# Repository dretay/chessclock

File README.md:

# Trip countdown frame

A little touchscreen picture frame that counts down to your next trip: the days left on flip-clock
cards over a living picture of where you're going. The scene follows the time of day (dawn, noon,
dusk, night), with lights coming on in its windows, water rippling, smoke rising, mist in the valley,
birds and fireflies, fireworks after dark, and between them the trip's own screens: live ride wait
times, the weather there, where your ship is. It runs on a [Lichee Pi Nano](https://wiki.sipeed.com/soft/Lichee/zh/Nano-Doc-Backup/get_started/first_eye.html)
(a tiny Allwinner F1C100s board: an ARM9, 32 MB of RAM) with a 5" 800x480 touch screen.

And a **scene editor** on the Mac to make your own: drop in a photo of where you're going, and the
**Scene Builder** makes its dusk and night, finds the sky, the water and the windows, and lets you add
lights, effects and screens, watching the result live in a preview window, then install it on the
frame over USB.

## On the frame

* **The countdown:** days to go on flip-clock cards (parchment, black split-flap, wood, a departure
  board), the hours and minutes on the last day, and the trip's own greeting once you're there ("Bon
  voyage!", "Have a magical day!").
* **A living scene**, blended from day, dusk and night pictures by the real time, with effects drawn in
  C fast enough for the little ARM9: window lights that switch on and off, lights on a sphere playing
  light shows, water, foam, smoke, mist, birds, fireflies, fireworks and a nightly show.
* **Screens in turn** with the countdown: a park's live ride waits ([ThemeParks.wiki](https://themeparks.wiki)),
  a 10-day forecast with rain and snow ([Open-Meteo](https://open-meteo.com)), a map of the Disney ships
  placed by their itineraries.
* **Touch settings:** the trip's date, fireworks, which rides, display brightness by day and night,
  WiFi, and switching between trips.
* **Signed apps:** each trip is an app, signed with your key; the frame can be locked to signed apps
  (developer mode off), and can install them from your own catalog over WiFi.

The apps here: **a Disney cruise**, **Magic Kingdom**, **EPCOT**, **Universal**, **a backpacking trip**,
and **New York City**.

## On the Mac: preview and Scene Builder

```sh
tools/setup.sh                       # once: Python (uv), the fonts; --ai for "find automatically"
tools/preview/preview.py castle      # the app running in a window, the mouse as the touchscreen
```

The preview runs the real app with the device's own drawing code. Its **Controls** set the time of
day, fire the fireworks, birds or fireflies, and (**Remote**) do the same on the frame over USB. Its
**Scene Builder** panel, docked beside it:

* **New…** a trip (a name, a park's ride waits, a place's weather), or pick an existing one;
* **Photos:** drop a photo to try it as the scene (each a trial, kept in the app when you like it);
  zoomed in, you paint on the original photo at full resolution;
* **Layout:** where the countdown sits, its size, the card style, the horizon;
* **Effects:** lights on a sphere and their shows; window lights (painted, boxed, found, with frames
  kept dark in front and windows grouped to switch together); water and foam; smoke, mist and birds;
  fireworks and fireflies;
* **Screens:** ride waits, weather (place checked), the ship map, and for how long each shows;
* **On the device:** install it on the frame, signed or not.

Every change is saved as you go. More in [the tools](docs/tools.md).

## Hardware

| Part | Notes |
|---|---|
| [Lichee Pi Nano](https://wiki.sipeed.com/soft/Lichee/zh/Nano-Doc-Backup/get_started/first_eye.html) | Allwinner F1C100s, 32 MB RAM, boots from microSD; run at 600 MHz (its own 408: `CPU_MHZ` in the device's settings) |
| 5" 800x480 40-pin RGB TFT with 4-wire resistive touch | e.g. the F50GLQ24E22: its ribbon plugs straight into the Nano, the touch film's tail to the ribbon's last four pins |
| microSD card | any size; the image is about 200 MB |
| 5 V USB power and a micro-USB cable | the micro-USB port is also the tools' fast serial line to the Mac |
| *Optional:* an ESP32 | WiFi, on the SPI bus ([wifi](docs/wifi.md)), for live waits, weather, ship positions, the catalog and the clock |
| *Optional:* a PAM8403 amplifier and a speaker | sound, from the chip's own audio codec ([system](docs/system.md)) |
| *Optional:* the [3D-printed enclosure](hardware/enclosure) | picture frame, back cover and desk cradle |
| *Optional:* a 3.3 V USB-serial adapter | the console on UART0, 115200 baud |

A custom board with the 64 MB F1C200s, the ESP32, the amplifier and room to tinker is designed in
[hardware/protoboard](hardware/protoboard). The board has no battery-backed clock: the frame keeps the
time on the SD card across power cuts, and sets it from the network with WiFi.

## Building and flashing

```sh
tools/build/build.sh --wifi                      # the base system (the first time: 1-2 hours)
tools/board/flash_sd.sh --all build/images-wifi  # the SD card (macOS; asks first)
tools/board/deploy.py --signed system countdown castle   # then apps go over USB: no reflashing
```

The SD card holds a read-only base system and, on a partition of their own, the apps and their
settings: changing an app never means rebuilding the image, and reflashing the base keeps the apps.
[Building and flashing](docs/building.md) has the details. `tools/test/check.py` checks everything,
rendering every scene and comparing it pixel for pixel with the last time.

## Documentation

| | |
|---|---|
| [docs/countdown.md](docs/countdown.md) | the countdown apps: their scenes, effects, screens and settings |
| [docs/tools.md](docs/tools.md) | the Mac tools: setup, the preview and Scene Builder, deploying, checking |
| [docs/apps.md](docs/apps.md) | what an app is: laid out, started, switched, signed, installed, the catalog, developer mode |
| [docs/system.md](docs/system.md) | how the system works: kernel, device tree, boot, memory, sound, security |
| [docs/wifi.md](docs/wifi.md) | WiFi through an ESP32: wiring, firmware, the wiring check and wiring test |
| [docs/building.md](docs/building.md) | building the base system and flashing the card |
| [apps/countdown/README.md](apps/countdown/README.md) | the countdown runtime |
| [tools/themegen/README.md](tools/themegen/README.md) | how scenes are made and packed |
| [hardware/](hardware) | the enclosure, and the protoboard (KiCad) |

## Repository layout

| Path | |
|---|---|
| `apps/` | one folder per app (`app.json`, `run`, its scene): `cruise`, `castle`, `epcot`, `universal`, `backpacking`, `new-york-city`; `countdown` (the runtime the trips share: the countdown, its screens and their fetchers) and `system` (what every app shares: the C drawing library, Settings, Device settings, WiFi, the picker) |
| `tools/preview/` | the preview window (Swift), the Scene Builder (a web page in it), and the server between them |
| `tools/themegen/` | making scenes from photos (`photo_scene.py`), packing them (`scene_pack.py`), icons, splashes, the ship map |
| `tools/apps/` | new apps, packing and signing them, publishing the catalog |
| `tools/board/` | talking to the board over USB: deploy, run, flash the card |
| `tools/build/` | incremental base-system builds in a container |
| `tools/wifi/` | the ESP32's WiFi firmware, and its wiring-test firmware |
| `tools/test/` | the checks |
| `board/licheepi_nano/`, `configs/`, `package/` | the Buildroot `BR2_EXTERNAL` tree: kernel config, patches and device tree, U-Boot, the SD card layout, the boot scripts (Buildroot itself is unmodified) |
| `hardware/` | the enclosure and the protoboard |
| `docs/` | the documentation above |
| `pyproject.toml`, `uv.lock`, `.python-version` | the Mac tools' Python (`tools/setup.sh`) |
| `Dockerfile.base` | the base image: the cross-compiler and a first build (then `tools/build/build.sh`) |
| `assets/` | (not in the repository) source photos and fonts |

## Credits

The Buildroot setup started from [unframework/licheepi-nano-buildroot](https://github.com/unframework/licheepi-nano-buildroot), which in turn adapted the FunKey Zero project's [buildroot-licheepi-zero](https://github.com/Squonk42/buildroot-licheepi-zero/). The F1C100s kernel and U-Boot work comes from @Icenowy, @Lichee-Pi and @unframework. Ride waits from [ThemeParks.wiki](https://themeparks.wiki), weather from [Open-Meteo](https://open-meteo.com), ship schedules from [CruiseMapper](https://www.cruisemapper.com). The scenes made from photos of Disney and Universal parks and ships are for personal use; Disney and Universal names and places are their owners' trademarks.

Licensed under the GPL-3.0 (see [LICENSE](LICENSE)).

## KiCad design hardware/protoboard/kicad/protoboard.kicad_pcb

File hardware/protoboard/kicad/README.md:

# F1C200s protoboard - KiCad project

KiCad 10 project for the board specified in [`../DESIGN.md`](../DESIGN.md):
118 x 72.5 mm, 4 layers: F.Cu signals + GND pour / In1 solid GND (no tracks) /
In2 signals + +3V3 pour / B.Cu signals + GND pour.

| File | |
|---|---|
| `protoboard.kicad_pro` | project, design rules (0.127 mm clearance, 0.1 mm min track for the router's neck-downs at the QFN, 0.2 mm drill) and netclasses (Default, Power, HighCurrent, USB) |
| `protoboard.kicad_sch` | root sheet, with sub-sheets `power`, `soc`, `display`, `storage`, `wifi`, `audio`, `io` |
| `protoboard.kicad_pcb` | placed for the desk stand (LCD connector front-right, USB-C/microSD/5V IN on the back edge) and autorouted, 5 connections left by hand (see below), pours filled, ESP antenna keep-out |
| `lib/` | custom symbols (F1C200s, SY8089, PT4103, NS2009, ESP32-C3 SuperMini) and footprints (SuperMini for headers or flat soldering, F1C QFN-88 with 0.22 mm pads, prototyping grid, rail strips) |
| `gen/` | the generator |

## Generated, not hand-drawn

`gen/design.py` holds the whole netlist: every part, value, footprint and
pin-to-net assignment, block by block following DESIGN.md. The rest is
derived from it:

```sh
./gen/build.sh            # libs -> schematic -> netlist -> PCB, then ERC + DRC (reports in gen/.cache/)
./gen/build.sh --sch-only # stop after the schematic
```

* `gen_sch.py` places the symbols on each sheet and connects every pin with a
  power symbol, a label or a no-connect flag. Nothing is wired, so
  connectivity comes only from net names.
* `gen_pcb.py` (run with KiCad's own Python) reads the netlist KiCad exports
  from the schematic, so the board stays in parity with it. It fixes the parts
  whose position the spec decides (FPC, USB-C, microSD, ESP, buttons,
  breakouts, rails, holes) and packs the rest as close as possible to the pads
  they connect to.

**Rerunning `build.sh` overwrites the .kicad_sch and .kicad_pcb files.** Once
you start routing or moving parts by hand, stop regenerating the PCB: make
schematic changes in KiCad and use *Update PCB from Schematic*. Or keep
editing `design.py`, but only with `--sch-only`.

## Routing

The board was autorouted with [Freerouting](https://github.com/freerouting/freerouting)
2.5 (needs Java 25+):

```sh
FREEROUTING_JAR=/path/to/freerouting.jar JAVA=/path/to/java ./gen/route.sh 40        # fresh route
FREEROUTING_JAR=... KEEP_TRACKS=1 ./gen/route.sh 40                                   # continue from the current tracks
WORK=gen/.cache/try1 ./gen/route.sh                                                   # route a copy instead
```

`route.sh` exports a Specctra DSN (`route.py export`, with pours and
stitching vias stripped), runs Freerouting with `gen/freerouting.rules`
(In1 inactive, so the GND plane gets vias but no tracks), imports the session,
then in a fresh process (`route.py post`) fixes undersized via rings, pours
+3V3 on In2 and GND on F.Cu/B.Cu, adds GND stitching vias wherever one fits
inside an outer pour, refills, and finally removes any via DRC flags as
dangling or (for GND vias) too close to something (two rounds: removing a
via can leave a neighbour dangling).

`build.sh` refuses to regenerate a routed board (`FORCE=1` overrides, which
throws the routing away). `gen_pcb.py` reproduces the routed board's
placement exactly, so a reroute is `FORCE=1 ./gen/build.sh` then
`./gen/route.sh 30`.

### What made it routable

Freerouting gets almost all of its result in the first run: continuation
passes (`KEEP_TRACKS=1`) never improved a board, and two runs of the same
placement differed by 22 vs 56 unconnected, so it pays to try several
placements in parallel (one core each) rather than run one longer. Fixes:

* **Board 118 x 72.5 mm and 0.25 mm extra spacing around every part**
  (`BOARD_W`, `BOARD_H`, `PLACE_GAP` in `gen_pcb.py`). On the stand layout
  0.25 gave 5 unconnected where 0.15/0.2 gave 14-57.
* **SoC rotated 180 degrees** (`SOC_ROT`): the LCD connector is right of the
  chip, and 180 lets the power pins escape far better than 90 (13 vs 28+).
* **Buck order** (`BUCK_X`): the three SY8089 bucks along the front edge.
* **microSD on the back edge.** `SD_SIDE=1` puts it on the right edge instead
  (and gives the protogrid back its full 38 columns, rails 32 holes), but the
  best of six routes was 19 unconnected against 5, so it isn't the default.
* **+1V1 area on In2** (added by `route.py post`, priority over the +3V3
  pour) from the core buck to under the SoC, plus `gen/viafix.py`, which
  drops a via into it from any +1V1 pad or track end the router left.
* **0.5 mm no-track strip** along the board edges (the router hugged them).
* **Ribbon keep-out:** connectors, switches and through-hole parts stay out
  of the area the LCD ribbon lies over between the front edge and the FPC.
* **QFN fan-out area:** the strip between the SoC and the FPC is kept free
  of parts for the LCD lines and their vias.
* **Placement order:** crystal and its caps first, then the SoC decoupling
  caps, each one next to a power pin of its own chip.
* **In1 stays a solid plane.** Letting the router use In1 (`gen/freerouting_in1.rules`)
  got to 7 unconnected on its own but broke the GND plane into 44 islands,
  so it isn't used.

### Finishing by hand

* **+2V5, SoC pin 36:** a 0.8 mm gap to its own track end; the straight line
  passes +1V1 pin 35, so come in from outside the pin row.
* **RESET (2):** SoC pin 70 to its pull-up R16, and R16 to the RESET button's
  track on B.Cu (stub at x 47.5, y 31).
* **GND (2):** two pour islands; KiCad's ratsnest shows them - a via each.
* 199 `track_width` are the router's 0.112 mm neck-downs into the QFN pads
  (allowed by the 0.1 mm board minimum, flagged against the netclass width).
* Silkscreen overlaps.

## State

* ERC: 0 violations. DRC: 0 clearance, short or courtyard errors, schematic
  parity clean; 5 unconnected, listed above.
* Test points are on the bottom side.
* R/C/L designators are on F.Fab (the assembly drawing). The board is too
  dense for them on silk.
* Open items are listed at the end of DESIGN.md.

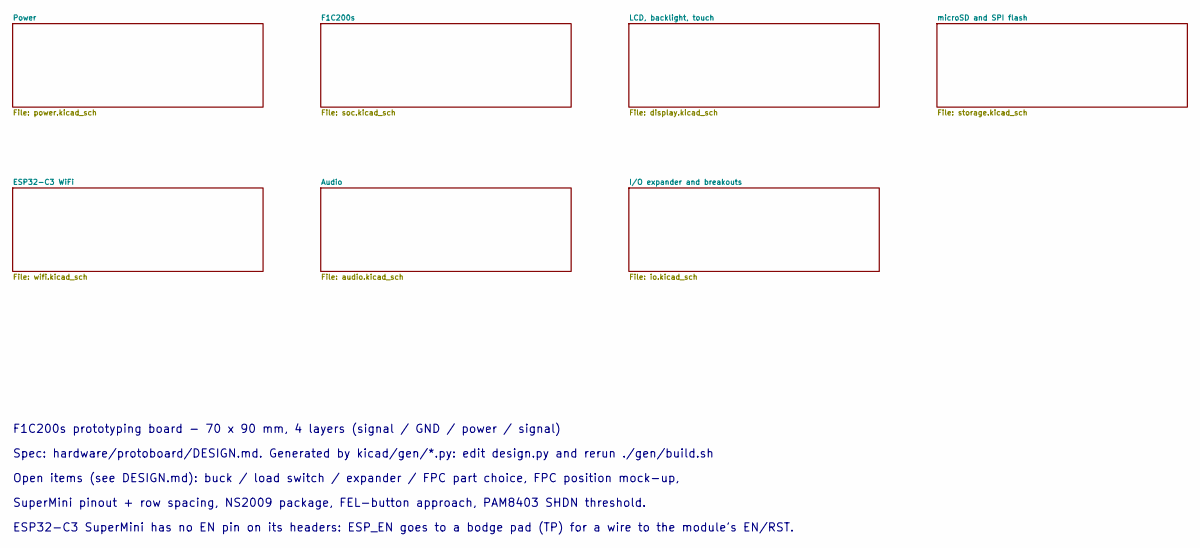
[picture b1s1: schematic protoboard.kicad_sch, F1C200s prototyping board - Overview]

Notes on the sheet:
F1C200s prototyping board - 70 x 90 mm, 4 layers (signal / GND / power / signal)
Spec: hardware/protoboard/DESIGN.md. Generated by kicad/gen/*.py: edit design.py and rerun ./gen/build.sh
Open items (see DESIGN.md): buck / load switch / expander / FPC part choice, FPC position mock-up,
SuperMini pinout + row spacing, NS2009 package, FEL-button approach, PAM8403 SHDN threshold.
ESP32-C3 SuperMini has no EN pin on its headers: ESP_EN goes to a bodge pad (TP) for a wire to the module's EN/RST.

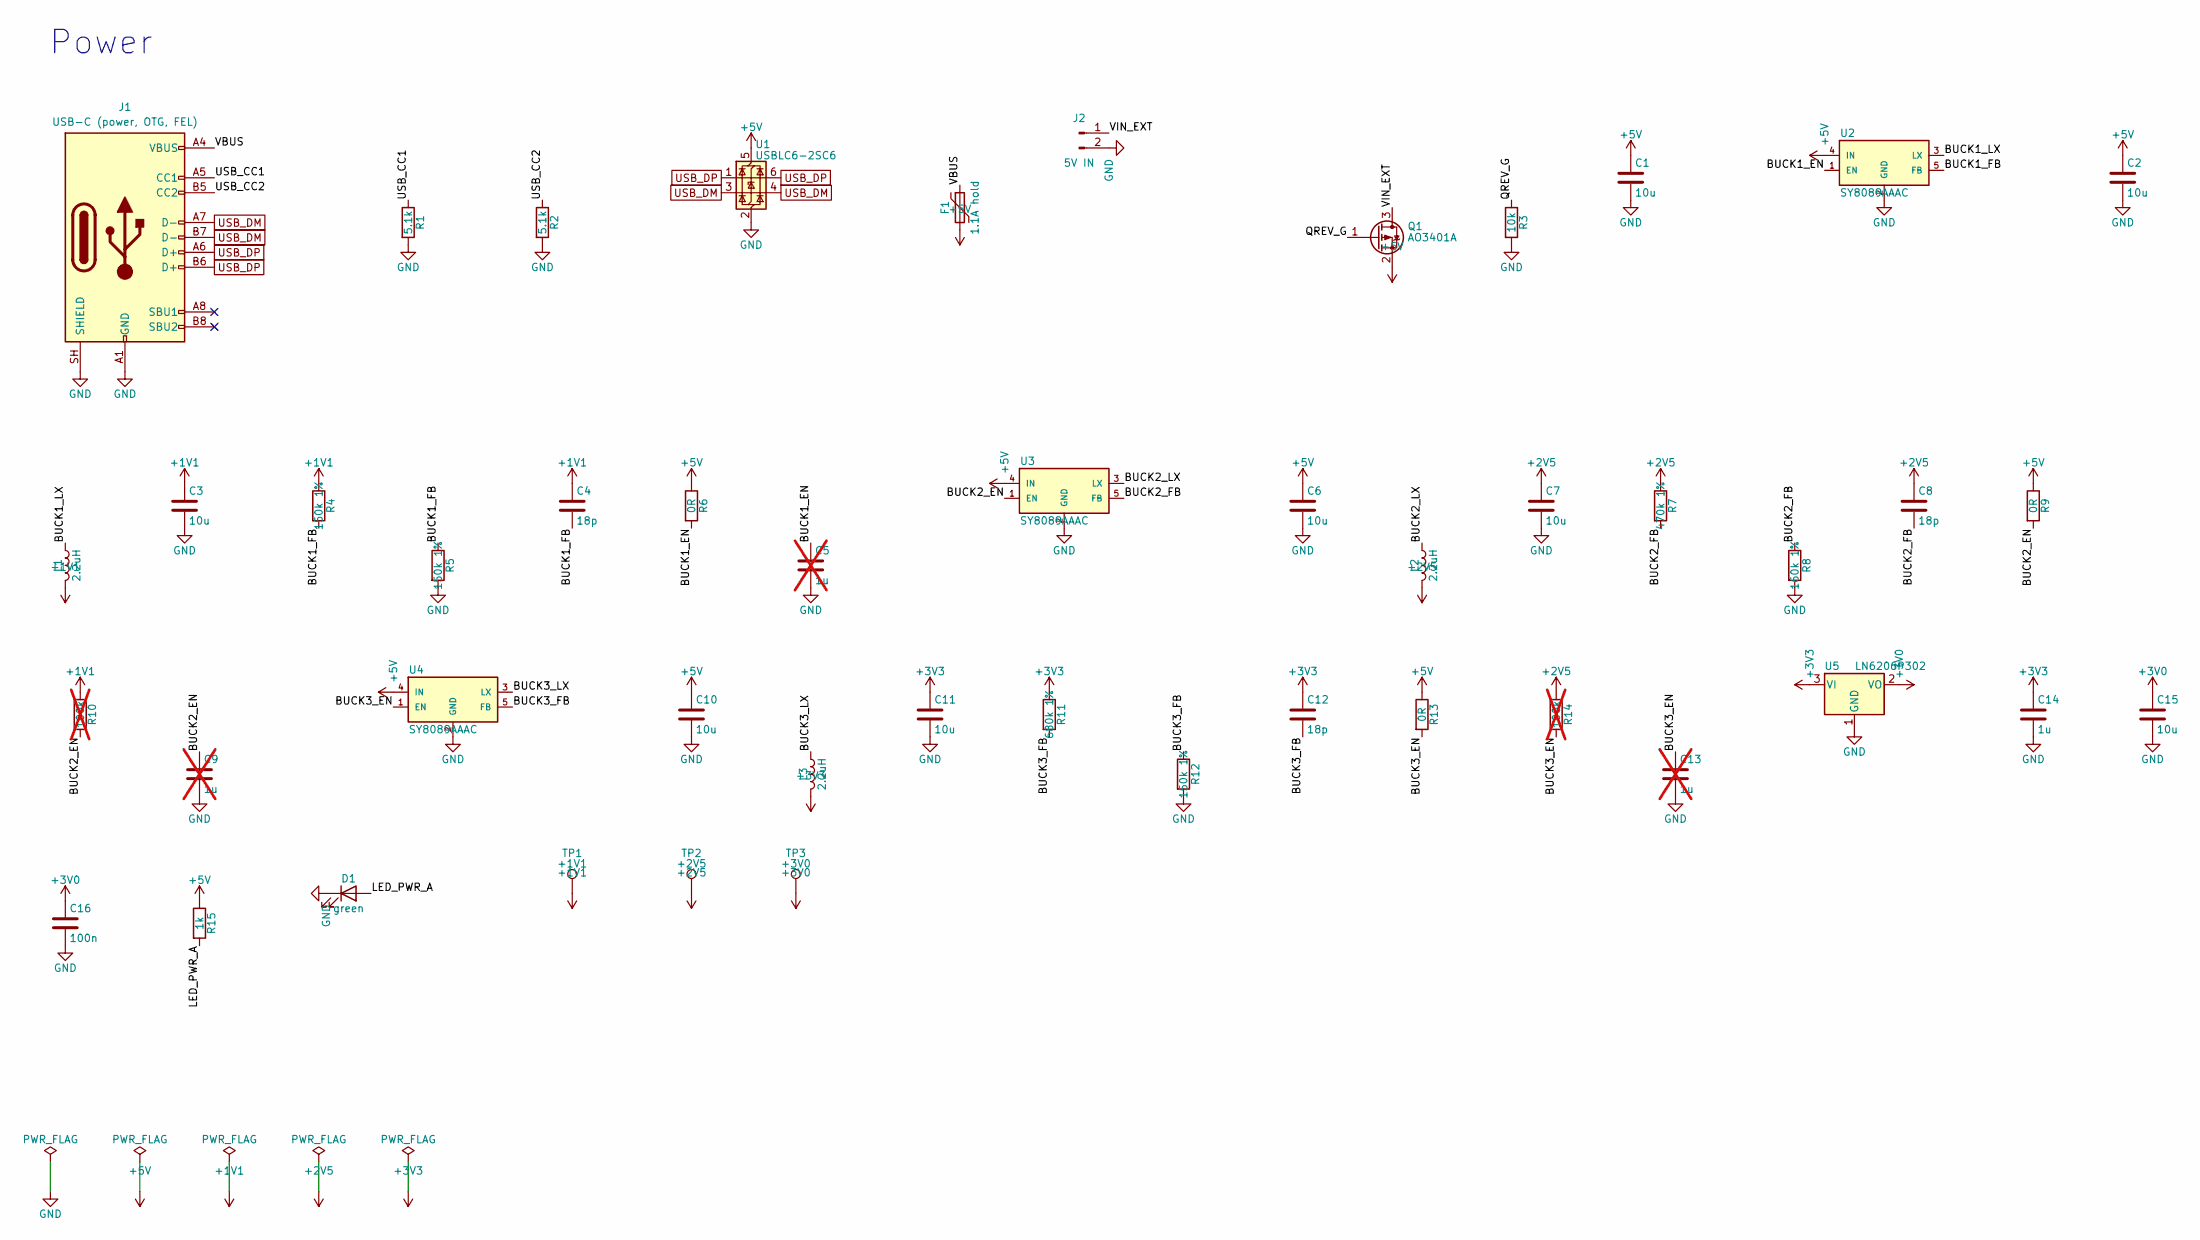
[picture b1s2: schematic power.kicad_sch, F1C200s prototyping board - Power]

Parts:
C1, C2, C3, C6, C7, C10, C11: 10u; C_1206_3216Metric_Pad1.33x1.80mm_HandSolder
C4, C8, C12: 18p; C_0805_2012Metric_Pad1.18x1.45mm_HandSolder
C5, C9, C13: 1u; C_0805_2012Metric_Pad1.18x1.45mm_HandSolder; not fitted
C14: 1u; C_0805_2012Metric_Pad1.18x1.45mm_HandSolder
C15: 10u; C_0805_2012Metric_Pad1.18x1.45mm_HandSolder
C16: 100n; C_0805_2012Metric_Pad1.18x1.45mm_HandSolder
D1: green; LED_0805_2012Metric_Pad1.15x1.40mm_HandSolder
F1: 1.1A hold; Fuse_1206_3216Metric_Pad1.42x1.75mm_HandSolder
J1: USB-C (power, OTG, FEL); USB_C_Receptacle_HRO_TYPE-C-31-M-12
J2: 5V IN; TerminalBlock_Phoenix_PT-1,5-2-3.5-H_1x02_P3.50mm_Horizontal
L1, L2, L3: 2.2uH; L_Bourns-SRN4018
Q1: AO3401A; SOT-23
R1, R2: 5.1k; R_0805_2012Metric_Pad1.20x1.40mm_HandSolder
R3: 10k; R_0805_2012Metric_Pad1.20x1.40mm_HandSolder
R4, R5, R12: 150k 1%; R_0805_2012Metric_Pad1.20x1.40mm_HandSolder
R6, R9, R13: 0R; R_0805_2012Metric_Pad1.20x1.40mm_HandSolder
R7: 470k 1%; R_0805_2012Metric_Pad1.20x1.40mm_HandSolder
R8: 160k 1%; R_0805_2012Metric_Pad1.20x1.40mm_HandSolder
R10, R14: 100k; R_0805_2012Metric_Pad1.20x1.40mm_HandSolder; not fitted
R11: 680k 1%; R_0805_2012Metric_Pad1.20x1.40mm_HandSolder
R15: 1k; R_0805_2012Metric_Pad1.20x1.40mm_HandSolder
TP1: +1V1; TestPoint_Pad_D1.5mm
TP2: +2V5; TestPoint_Pad_D1.5mm
TP3: +3V0; TestPoint_Pad_D1.5mm
U1: USBLC6-2SC6; SOT-23-6
U2, U3, U4: SY8089AAAC; SOT-23-5
U5: LN6206P302; SOT-23-3

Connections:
+1V1: C3.1, C4.1, L1.2, R4.1, R10.1, TP1.1; also elsewhere on the board
+2V5: C7.1, C8.1, L2.2, R7.1, R14.1, TP2.1; also elsewhere on the board
+3V0: C15.1, C16.1, TP3.1, U5.2 (VO); also elsewhere on the board
+3V3: C11.1, C12.1, C14.1, L3.2, R11.1, U5.3 (VI); also elsewhere on the board
+5V: C1.1, C2.1, C6.1, C10.1, F1.2, Q1.2 (S), R6.1, R9.1, R13.1, R15.1, U1.5 (VBUS), U2.4 (IN), U3.4 (IN), U4.4 (IN); also elsewhere on the board
/Power/BUCK1_EN: C5.1, R6.2, U2.1 (EN)
/Power/BUCK1_FB: C4.2, R4.2, R5.1, U2.5 (FB)
/Power/BUCK1_LX: L1.1, U2.3 (LX)
/Power/BUCK2_EN: C9.1, R9.2, R10.2, U3.1 (EN)
/Power/BUCK2_FB: C8.2, R7.2, R8.1, U3.5 (FB)
/Power/BUCK2_LX: L2.1, U3.3 (LX)
/Power/BUCK3_EN: C13.1, R13.2, R14.2, U4.1 (EN)
/Power/BUCK3_FB: C12.2, R11.2, R12.1, U4.5 (FB)
/Power/BUCK3_LX: L3.1, U4.3 (LX)
/Power/LED_PWR_A: D1.2 (A), R15.2
/Power/QREV_G: Q1.1 (G), R3.1
/Power/USB_CC1: J1.A5 (CC1), R1.1
/Power/USB_CC2: J1.B5 (CC2), R2.1
/Power/VBUS: F1.1, J1.A4 (VBUS), J1.A9 (VBUS), J1.B4 (VBUS), J1.B9 (VBUS)
/Power/VIN_EXT: J2.1, Q1.3 (D)
GND: C1.2, C2.2, C3.2, C5.2, C6.2, C7.2, C9.2, C10.2, C11.2, C13.2, C14.2, C15.2, C16.2, D1.1 (K), J1.A1 (GND), J1.A12 (GND), J1.B1 (GND), J1.B12 (GND), J1.SH (SHIELD), J2.2, R1.2, R2.2, R3.2, R5.2, R8.2, R12.2, U1.2 (GND), U2.2 (GND), U3.2 (GND), U4.2 (GND), U5.1 (GND); also elsewhere on the board
USB_DM: J1.A7 (D-), J1.B7 (D-), U1.3 (I/O2), U1.4 (I/O2); also elsewhere on the board
USB_DP: J1.A6 (D+), J1.B6 (D+), U1.1 (I/O1), U1.6 (I/O1); also elsewhere on the board

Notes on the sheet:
Power

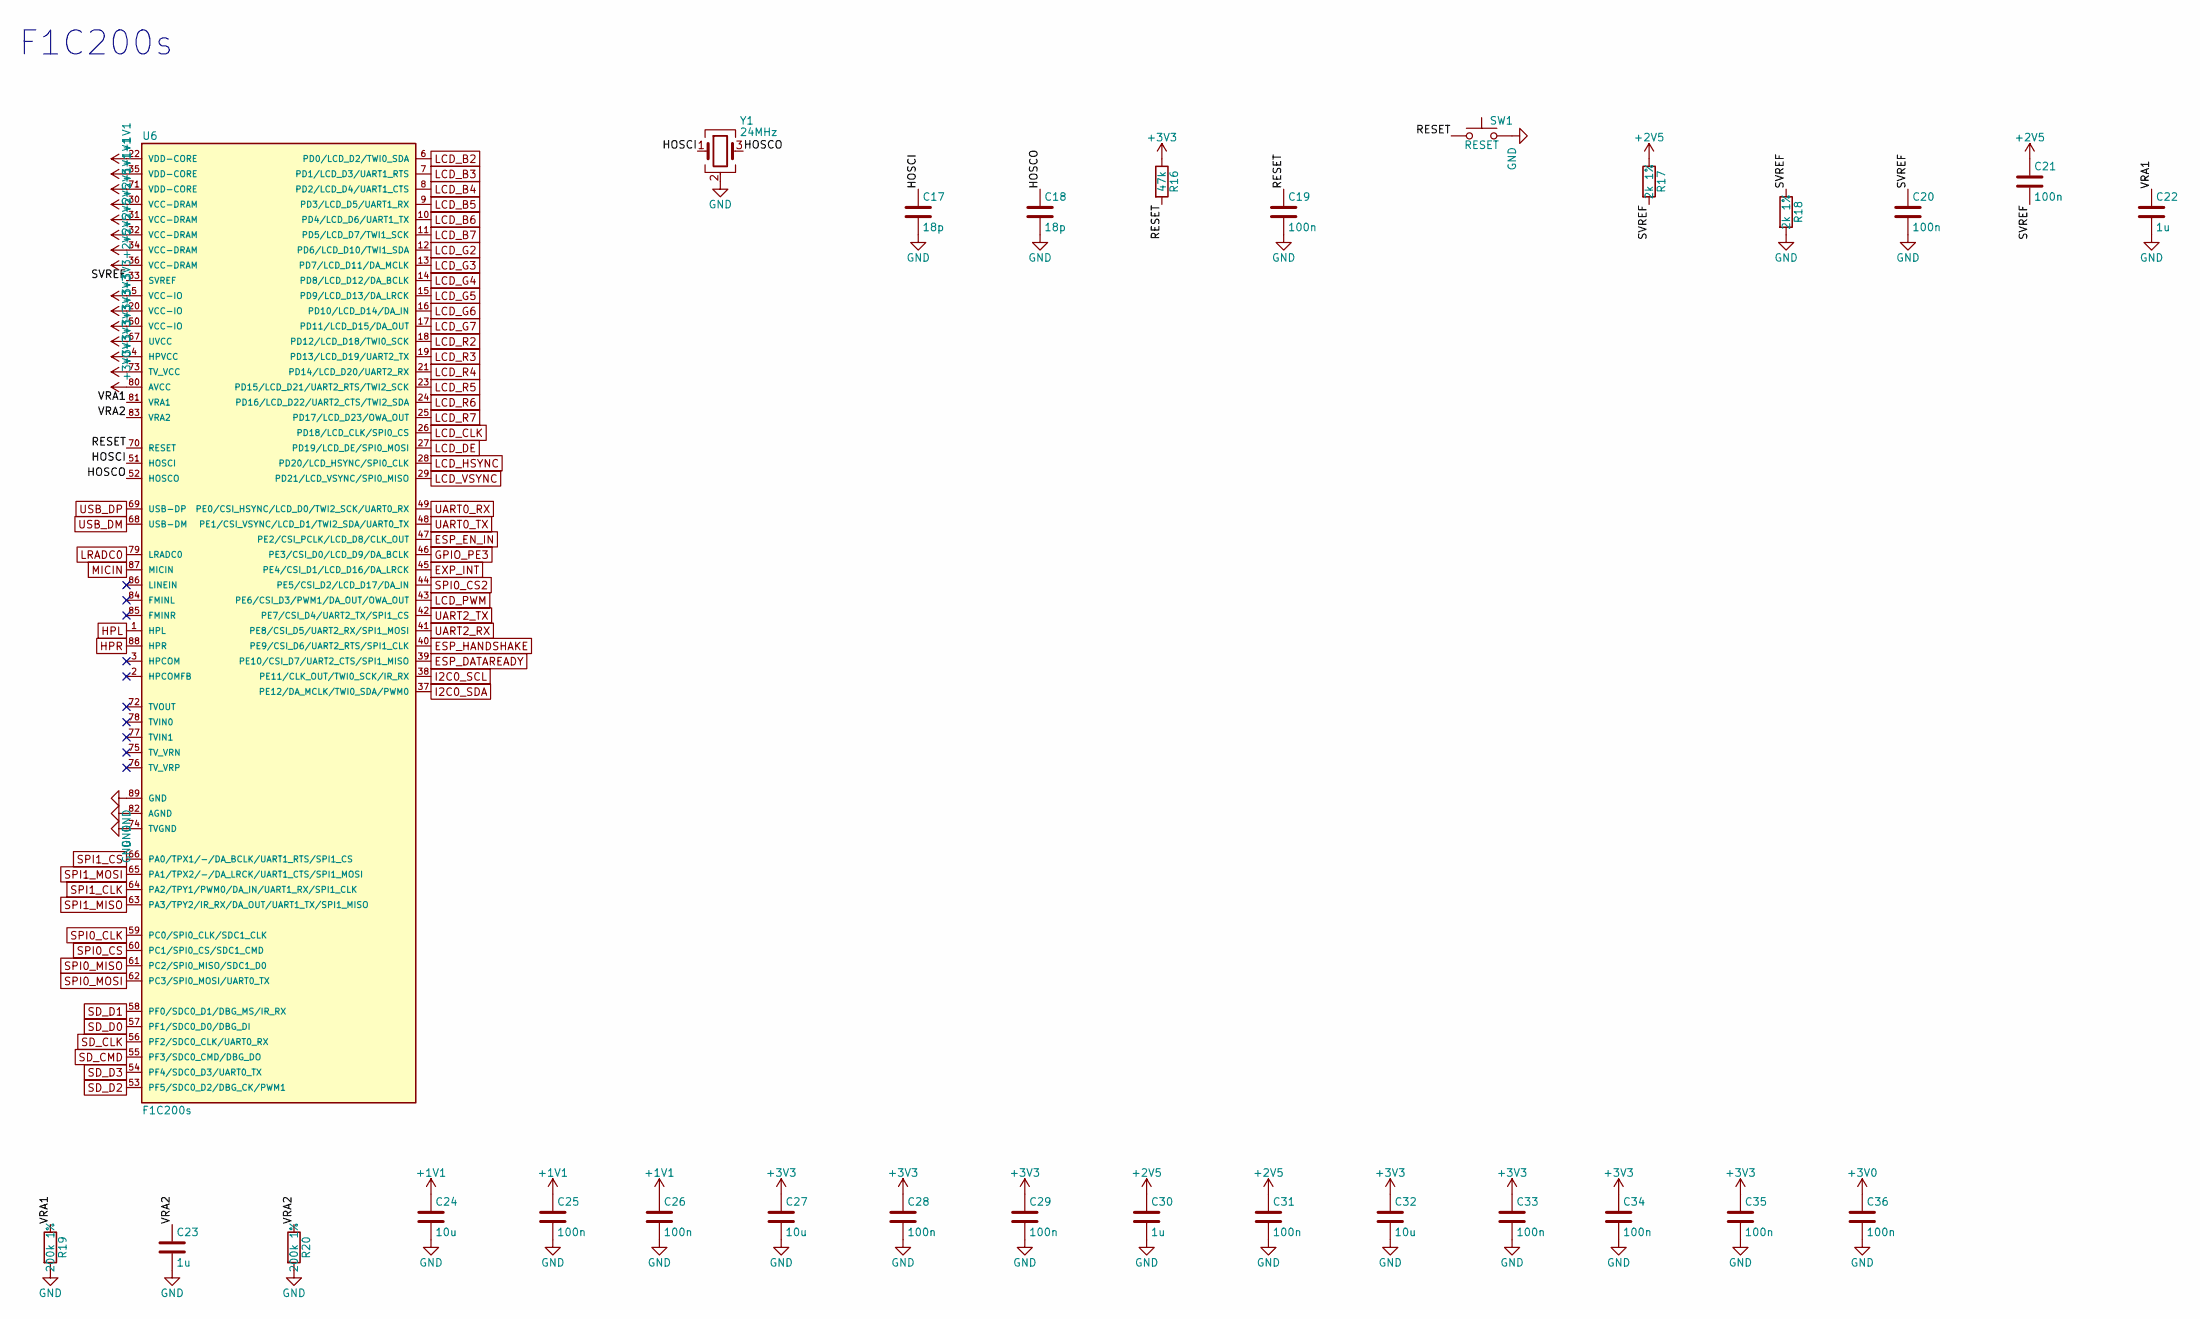
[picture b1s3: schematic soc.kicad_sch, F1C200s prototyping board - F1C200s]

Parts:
C17, C18: 18p; C_0805_2012Metric_Pad1.18x1.45mm_HandSolder
C19, C20, C21, C25, C26, C28, C29, C31, C33, C34, C35, C36: 100n; C_0805_2012Metric_Pad1.18x1.45mm_HandSolder
C22, C23, C30: 1u; C_0805_2012Metric_Pad1.18x1.45mm_HandSolder
C24, C27, C32: 10u; C_1206_3216Metric_Pad1.33x1.80mm_HandSolder
R16: 47k; R_0805_2012Metric_Pad1.20x1.40mm_HandSolder
R17, R18: 2k 1%; R_0805_2012Metric_Pad1.20x1.40mm_HandSolder
R19, R20: 200k 1%; R_0805_2012Metric_Pad1.20x1.40mm_HandSolder
SW1: RESET; SW_PUSH_6mm
U6: F1C200s; F1C200s_QFN-88-1EP_10x10mm_P0.4mm_EP6.74x6.74mm_ThermalVias
Y1: 24MHz; Crystal_SMD_3225-4Pin_3.2x2.5mm_HandSoldering

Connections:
+1V1: C24.1, C25.1, C26.1, U6.22 (VDD-CORE), U6.35 (VDD-CORE), U6.71 (VDD-CORE); also elsewhere on the board
+2V5: C21.1, C30.1, C31.1, R17.1, U6.30 (VCC-DRAM), U6.31 (VCC-DRAM), U6.32 (VCC-DRAM), U6.34 (VCC-DRAM), U6.36 (VCC-DRAM); also elsewhere on the board
+3V0: C36.1, U6.80 (AVCC); also elsewhere on the board
+3V3: C27.1, C28.1, C29.1, C32.1, C33.1, C34.1, C35.1, R16.1, U6.4 (HPVCC), U6.5 (VCC-IO), U6.20 (VCC-IO), U6.50 (VCC-IO), U6.67 (UVCC), U6.73 (TV_VCC); also elsewhere on the board
/F1C200s/HOSCI: C17.1, U6.51 (HOSCI), Y1.1
/F1C200s/HOSCO: C18.1, U6.52 (HOSCO), Y1.3
/F1C200s/RESET: C19.1, R16.2, SW1.1, U6.70 (RESET)
/F1C200s/SVREF: C20.1, C21.2, R17.2, R18.1, U6.33 (SVREF)
/F1C200s/VRA1: C22.1, R19.1, U6.81 (VRA1)
/F1C200s/VRA2: C23.1, R20.1, U6.83 (VRA2)
ESP_DATAREADY: U6.39 (PE10/CSI_D7/UART2_CTS/SPI1_MISO); also elsewhere on the board
ESP_EN_IN: U6.47 (PE2/CSI_PCLK/LCD_D8/CLK_OUT); also elsewhere on the board
ESP_HANDSHAKE: U6.40 (PE9/CSI_D6/UART2_RTS/SPI1_CLK); also elsewhere on the board
EXP_INT: U6.45 (PE4/CSI_D1/LCD_D16/DA_LRCK); also elsewhere on the board
GND: C17.2, C18.2, C19.2, C20.2, C22.2, C23.2, C24.2, C25.2, C26.2, C27.2, C28.2, C29.2, C30.2, C31.2, C32.2, C33.2, C34.2, C35.2, C36.2, R18.2, R19.2, R20.2, SW1.2, U6.74 (TVGND), U6.82 (AGND), U6.89 (GND), Y1.2 (G), Y1.4 (G); also elsewhere on the board
GPIO_PE3: U6.46 (PE3/CSI_D0/LCD_D9/DA_BCLK); also elsewhere on the board
HPL: U6.1 (HPL); also elsewhere on the board
HPR: U6.88 (HPR); also elsewhere on the board
I2C0_SCL: U6.38 (PE11/CLK_OUT/TWI0_SCK/IR_RX); also elsewhere on the board
I2C0_SDA: U6.37 (PE12/DA_MCLK/TWI0_SDA/PWM0); also elsewhere on the board
LCD_B2: U6.6 (PD0/LCD_D2/TWI0_SDA); also elsewhere on the board
LCD_B3: U6.7 (PD1/LCD_D3/UART1_RTS); also elsewhere on the board
LCD_B4: U6.8 (PD2/LCD_D4/UART1_CTS); also elsewhere on the board
LCD_B5: U6.9 (PD3/LCD_D5/UART1_RX); also elsewhere on the board
LCD_B6: U6.10 (PD4/LCD_D6/UART1_TX); also elsewhere on the board
LCD_B7: U6.11 (PD5/LCD_D7/TWI1_SCK); also elsewhere on the board
LCD_CLK: U6.26 (PD18/LCD_CLK/SPI0_CS); also elsewhere on the board
LCD_DE: U6.27 (PD19/LCD_DE/SPI0_MOSI); also elsewhere on the board
LCD_G2: U6.12 (PD6/LCD_D10/TWI1_SDA); also elsewhere on the board
LCD_G3: U6.13 (PD7/LCD_D11/DA_MCLK); also elsewhere on the board
LCD_G4: U6.14 (PD8/LCD_D12/DA_BCLK); also elsewhere on the board
LCD_G5: U6.15 (PD9/LCD_D13/DA_LRCK); also elsewhere on the board
LCD_G6: U6.16 (PD10/LCD_D14/DA_IN); also elsewhere on the board
LCD_G7: U6.17 (PD11/LCD_D15/DA_OUT); also elsewhere on the board
LCD_HSYNC: U6.28 (PD20/LCD_HSYNC/SPI0_CLK); also elsewhere on the board
LCD_PWM: U6.43 (PE6/CSI_D3/PWM1/DA_OUT/OWA_OUT); also elsewhere on the board
LCD_R2: U6.18 (PD12/LCD_D18/TWI0_SCK); also elsewhere on the board
LCD_R3: U6.19 (PD13/LCD_D19/UART2_TX); also elsewhere on the board
LCD_R4: U6.21 (PD14/LCD_D20/UART2_RX); also elsewhere on the board
LCD_R5: U6.23 (PD15/LCD_D21/UART2_RTS/TWI2_SCK); also elsewhere on the board
LCD_R6: U6.24 (PD16/LCD_D22/UART2_CTS/TWI2_SDA); also elsewhere on the board
LCD_R7: U6.25 (PD17/LCD_D23/OWA_OUT); also elsewhere on the board
LCD_VSYNC: U6.29 (PD21/LCD_VSYNC/SPI0_MISO); also elsewhere on the board
LRADC0: U6.79 (LRADC0); also elsewhere on the board
MICIN: U6.87 (MICIN); also elsewhere on the board
SD_CLK: U6.56 (PF2/SDC0_CLK/UART0_RX); also elsewhere on the board
SD_CMD: U6.55 (PF3/SDC0_CMD/DBG_DO); also elsewhere on the board
SD_D0: U6.57 (PF1/SDC0_D0/DBG_DI); also elsewhere on the board
SD_D1: U6.58 (PF0/SDC0_D1/DBG_MS/IR_RX); also elsewhere on the board
SD_D2: U6.53 (PF5/SDC0_D2/DBG_CK/PWM1); also elsewhere on the board
SD_D3: U6.54 (PF4/SDC0_D3/UART0_TX); also elsewhere on the board
SPI0_CLK: U6.59 (PC0/SPI0_CLK/SDC1_CLK); also elsewhere on the board
SPI0_CS: U6.60 (PC1/SPI0_CS/SDC1_CMD); also elsewhere on the board
SPI0_CS2: U6.44 (PE5/CSI_D2/LCD_D17/DA_IN); also elsewhere on the board
SPI0_MISO: U6.61 (PC2/SPI0_MISO/SDC1_D0); also elsewhere on the board
SPI0_MOSI: U6.62 (PC3/SPI0_MOSI/UART0_TX); also elsewhere on the board
SPI1_CLK: U6.64 (PA2/TPY1/PWM0/DA_IN/UART1_RX/SPI1_CLK); also elsewhere on the board
SPI1_CS: U6.66 (PA0/TPX1/-/DA_BCLK/UART1_RTS/SPI1_CS); also elsewhere on the board
SPI1_MISO: U6.63 (PA3/TPY2/IR_RX/DA_OUT/UART1_TX/SPI1_MISO); also elsewhere on the board
SPI1_MOSI: U6.65 (PA1/TPX2/-/DA_LRCK/UART1_CTS/SPI1_MOSI); also elsewhere on the board
UART0_RX: U6.49 (PE0/CSI_HSYNC/LCD_D0/TWI2_SCK/UART0_RX); also elsewhere on the board
UART0_TX: U6.48 (PE1/CSI_VSYNC/LCD_D1/TWI2_SDA/UART0_TX); also elsewhere on the board
UART2_RX: U6.41 (PE8/CSI_D5/UART2_RX/SPI1_MOSI); also elsewhere on the board
UART2_TX: U6.42 (PE7/CSI_D4/UART2_TX/SPI1_CS); also elsewhere on the board
USB_DM: U6.68 (USB-DM); also elsewhere on the board
USB_DP: U6.69 (USB-DP); also elsewhere on the board

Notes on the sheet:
F1C200s

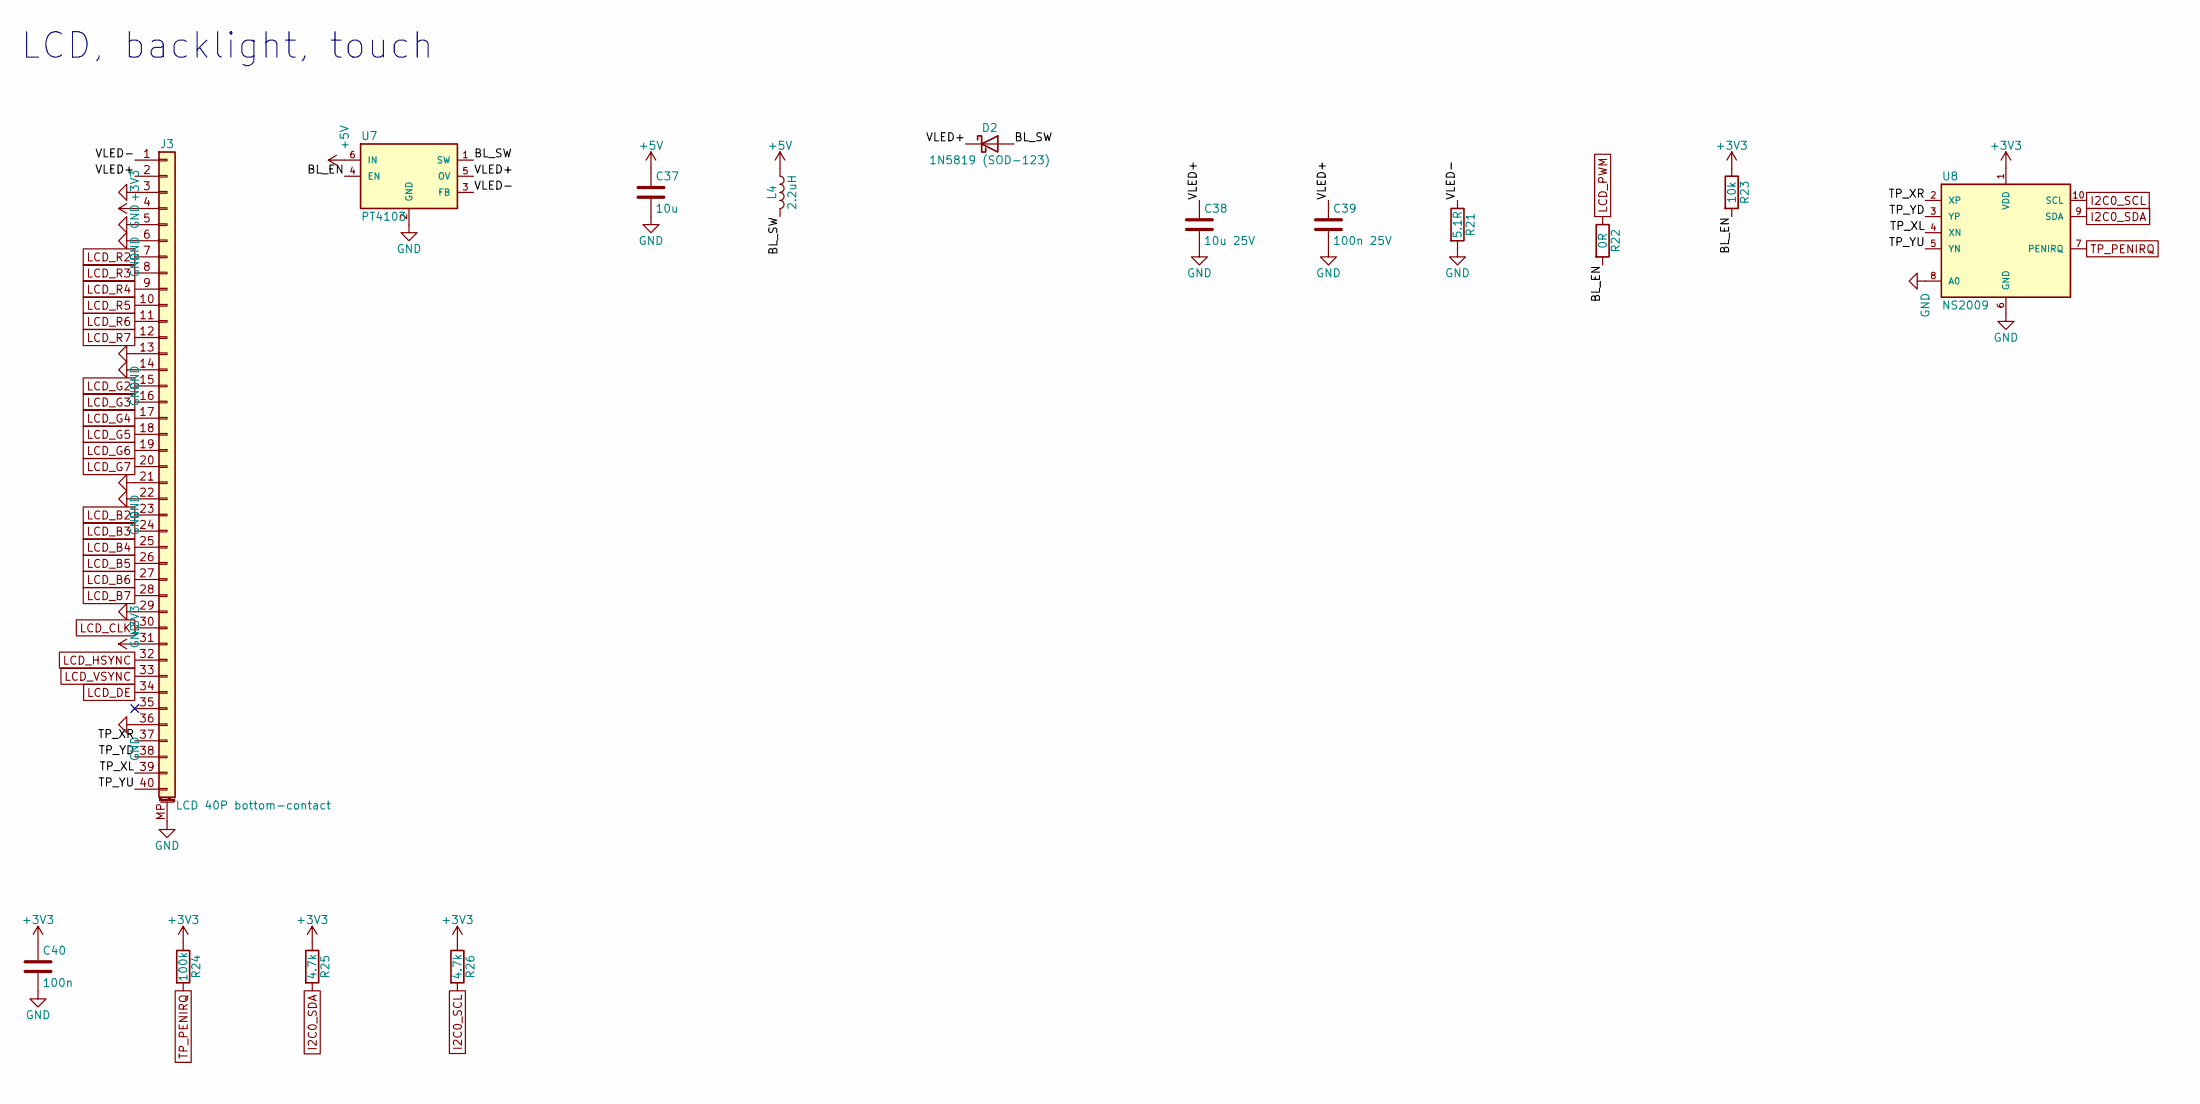
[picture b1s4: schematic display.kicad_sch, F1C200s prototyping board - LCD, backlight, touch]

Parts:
C37: 10u; C_1206_3216Metric_Pad1.33x1.80mm_HandSolder
C38: 10u 25V; C_1206_3216Metric_Pad1.33x1.80mm_HandSolder
C39: 100n 25V; C_0805_2012Metric_Pad1.18x1.45mm_HandSolder
C40: 100n; C_0805_2012Metric_Pad1.18x1.45mm_HandSolder
D2: 1N5819 (SOD-123); D_SOD-123
J3: LCD 40P bottom-contact; Hirose_FH12-40S-0.5SH_1x40-1MP_P0.50mm_Horizontal
L4: 2.2uH; L_Bourns-SRN4018
R21: 5.1R; R_0805_2012Metric_Pad1.20x1.40mm_HandSolder
R22: 0R; R_0805_2012Metric_Pad1.20x1.40mm_HandSolder
R23: 10k; R_0805_2012Metric_Pad1.20x1.40mm_HandSolder
R24: 100k; R_0805_2012Metric_Pad1.20x1.40mm_HandSolder
R25, R26: 4.7k; R_0805_2012Metric_Pad1.20x1.40mm_HandSolder
U7: PT4103; SOT-23-6
U8: NS2009; MSOP-10_3x3mm_P0.5mm

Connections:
+3V3: C40.1, J3.4, J3.31, R23.1, R24.1, R25.1, R26.1, U8.1 (VDD); also elsewhere on the board
+5V: C37.1, L4.1, U7.6 (IN); also elsewhere on the board
/LCD, backlight, touch/BL_EN: R22.2, R23.2, U7.4 (EN)
/LCD, backlight, touch/BL_SW: D2.2 (A), L4.2, U7.1 (SW)
/LCD, backlight, touch/TP_XL: J3.39, U8.4 (XN)
/LCD, backlight, touch/TP_XR: J3.37, U8.2 (XP)
/LCD, backlight, touch/TP_YD: J3.38, U8.3 (YP)
/LCD, backlight, touch/TP_YU: J3.40, U8.5 (YN)
/LCD, backlight, touch/VLED+: C38.1, C39.1, D2.1 (K), J3.2, U7.5 (OV)
/LCD, backlight, touch/VLED-: J3.1, R21.1, U7.3 (FB)
GND: C37.2, C38.2, C39.2, C40.2, J3.3, J3.5, J3.6, J3.13, J3.14, J3.21, J3.22, J3.29, J3.36, J3.MP (MountPin), R21.2, U7.2 (GND), U8.6 (GND), U8.8 (A0); also elsewhere on the board
I2C0_SCL: R26.2, U8.10 (SCL); also elsewhere on the board
I2C0_SDA: R25.2, U8.9 (SDA); also elsewhere on the board
LCD_B2: J3.23; also elsewhere on the board
LCD_B3: J3.24; also elsewhere on the board
LCD_B4: J3.25; also elsewhere on the board
LCD_B5: J3.26; also elsewhere on the board
LCD_B6: J3.27; also elsewhere on the board
LCD_B7: J3.28; also elsewhere on the board
LCD_CLK: J3.30; also elsewhere on the board
LCD_DE: J3.34; also elsewhere on the board
LCD_G2: J3.15; also elsewhere on the board
LCD_G3: J3.16; also elsewhere on the board
LCD_G4: J3.17; also elsewhere on the board
LCD_G5: J3.18; also elsewhere on the board
LCD_G6: J3.19; also elsewhere on the board
LCD_G7: J3.20; also elsewhere on the board
LCD_HSYNC: J3.32; also elsewhere on the board
LCD_PWM: R22.1; also elsewhere on the board
LCD_R2: J3.7; also elsewhere on the board
LCD_R3: J3.8; also elsewhere on the board
LCD_R4: J3.9; also elsewhere on the board
LCD_R5: J3.10; also elsewhere on the board
LCD_R6: J3.11; also elsewhere on the board
LCD_R7: J3.12; also elsewhere on the board
LCD_VSYNC: J3.33; also elsewhere on the board
TP_PENIRQ: R24.2, U8.7 (PENIRQ); also elsewhere on the board

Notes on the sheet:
LCD, backlight, touch

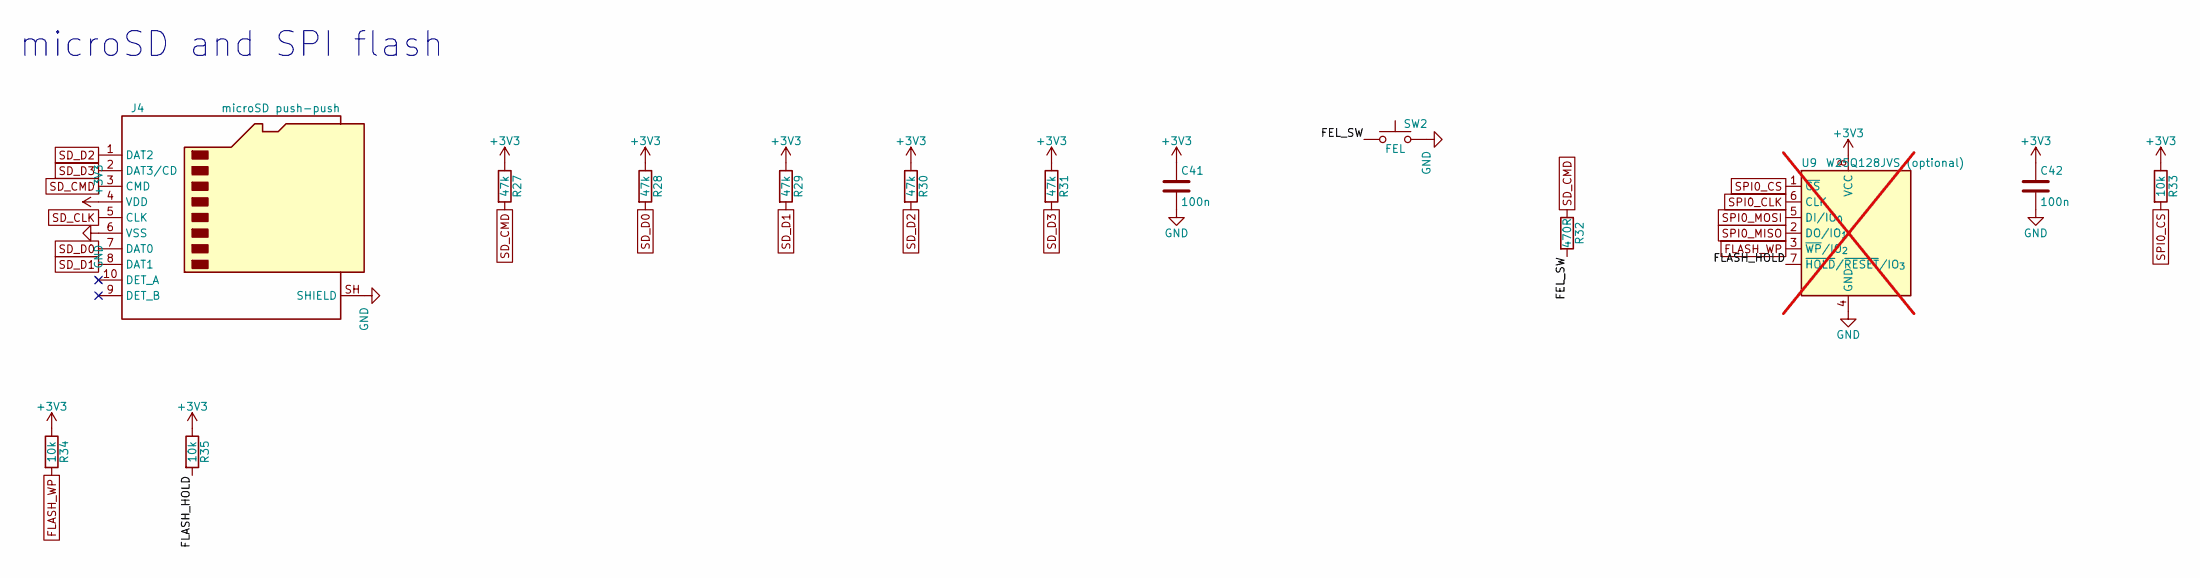
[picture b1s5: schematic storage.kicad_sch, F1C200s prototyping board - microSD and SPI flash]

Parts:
C41, C42: 100n; C_0805_2012Metric_Pad1.18x1.45mm_HandSolder
J4: microSD push-push; microSD_HC_Hirose_DM3AT-SF-PEJM5
R27, R28, R29, R30, R31: 47k; R_0805_2012Metric_Pad1.20x1.40mm_HandSolder
R32: 470R; R_0805_2012Metric_Pad1.20x1.40mm_HandSolder
R33, R34, R35: 10k; R_0805_2012Metric_Pad1.20x1.40mm_HandSolder
SW2: FEL; SW_PUSH_6mm
U9: W25Q128JVS (optional); SOIC-8_5.3x5.3mm_P1.27mm; not fitted

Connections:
+3V3: C41.1, C42.1, J4.4 (VDD), R27.1, R28.1, R29.1, R30.1, R31.1, R33.1, R34.1, R35.1, U9.8 (VCC); also elsewhere on the board
/microSD and SPI flash/FEL_SW: R32.2, SW2.1
/microSD and SPI flash/FLASH_HOLD: R35.2, U9.7 (~HOLD/~RESET/IO_{3})
FLASH_WP: R34.2, U9.3 (~WP/IO_{2}); also elsewhere on the board
GND: C41.2, C42.2, J4.6 (VSS), J4.SH (SHIELD), SW2.2, U9.4 (GND); also elsewhere on the board
SD_CLK: J4.5 (CLK); also elsewhere on the board
SD_CMD: J4.3 (CMD), R27.2, R32.1; also elsewhere on the board
SD_D0: J4.7 (DAT0), R28.2; also elsewhere on the board
SD_D1: J4.8 (DAT1), R29.2; also elsewhere on the board
SD_D2: J4.1 (DAT2), R30.2; also elsewhere on the board
SD_D3: J4.2 (DAT3/CD), R31.2; also elsewhere on the board
SPI0_CLK: U9.6 (CLK); also elsewhere on the board
SPI0_CS: R33.2, U9.1 (~CS); also elsewhere on the board
SPI0_MISO: U9.2 (DO/IO_{1}); also elsewhere on the board
SPI0_MOSI: U9.5 (DI/IO_{0}); also elsewhere on the board

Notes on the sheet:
microSD and SPI flash
